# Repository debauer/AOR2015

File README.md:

AOR2015 - Fahrzeug Sensorik und Musik
=======

Project splittet

https://github.com/debauer/uboot-hardware  
https://github.com/debauer/uboot-software  
https://github.com/debauer/uboot-laser-parts  
https://github.com/debauer/uboot-firmware

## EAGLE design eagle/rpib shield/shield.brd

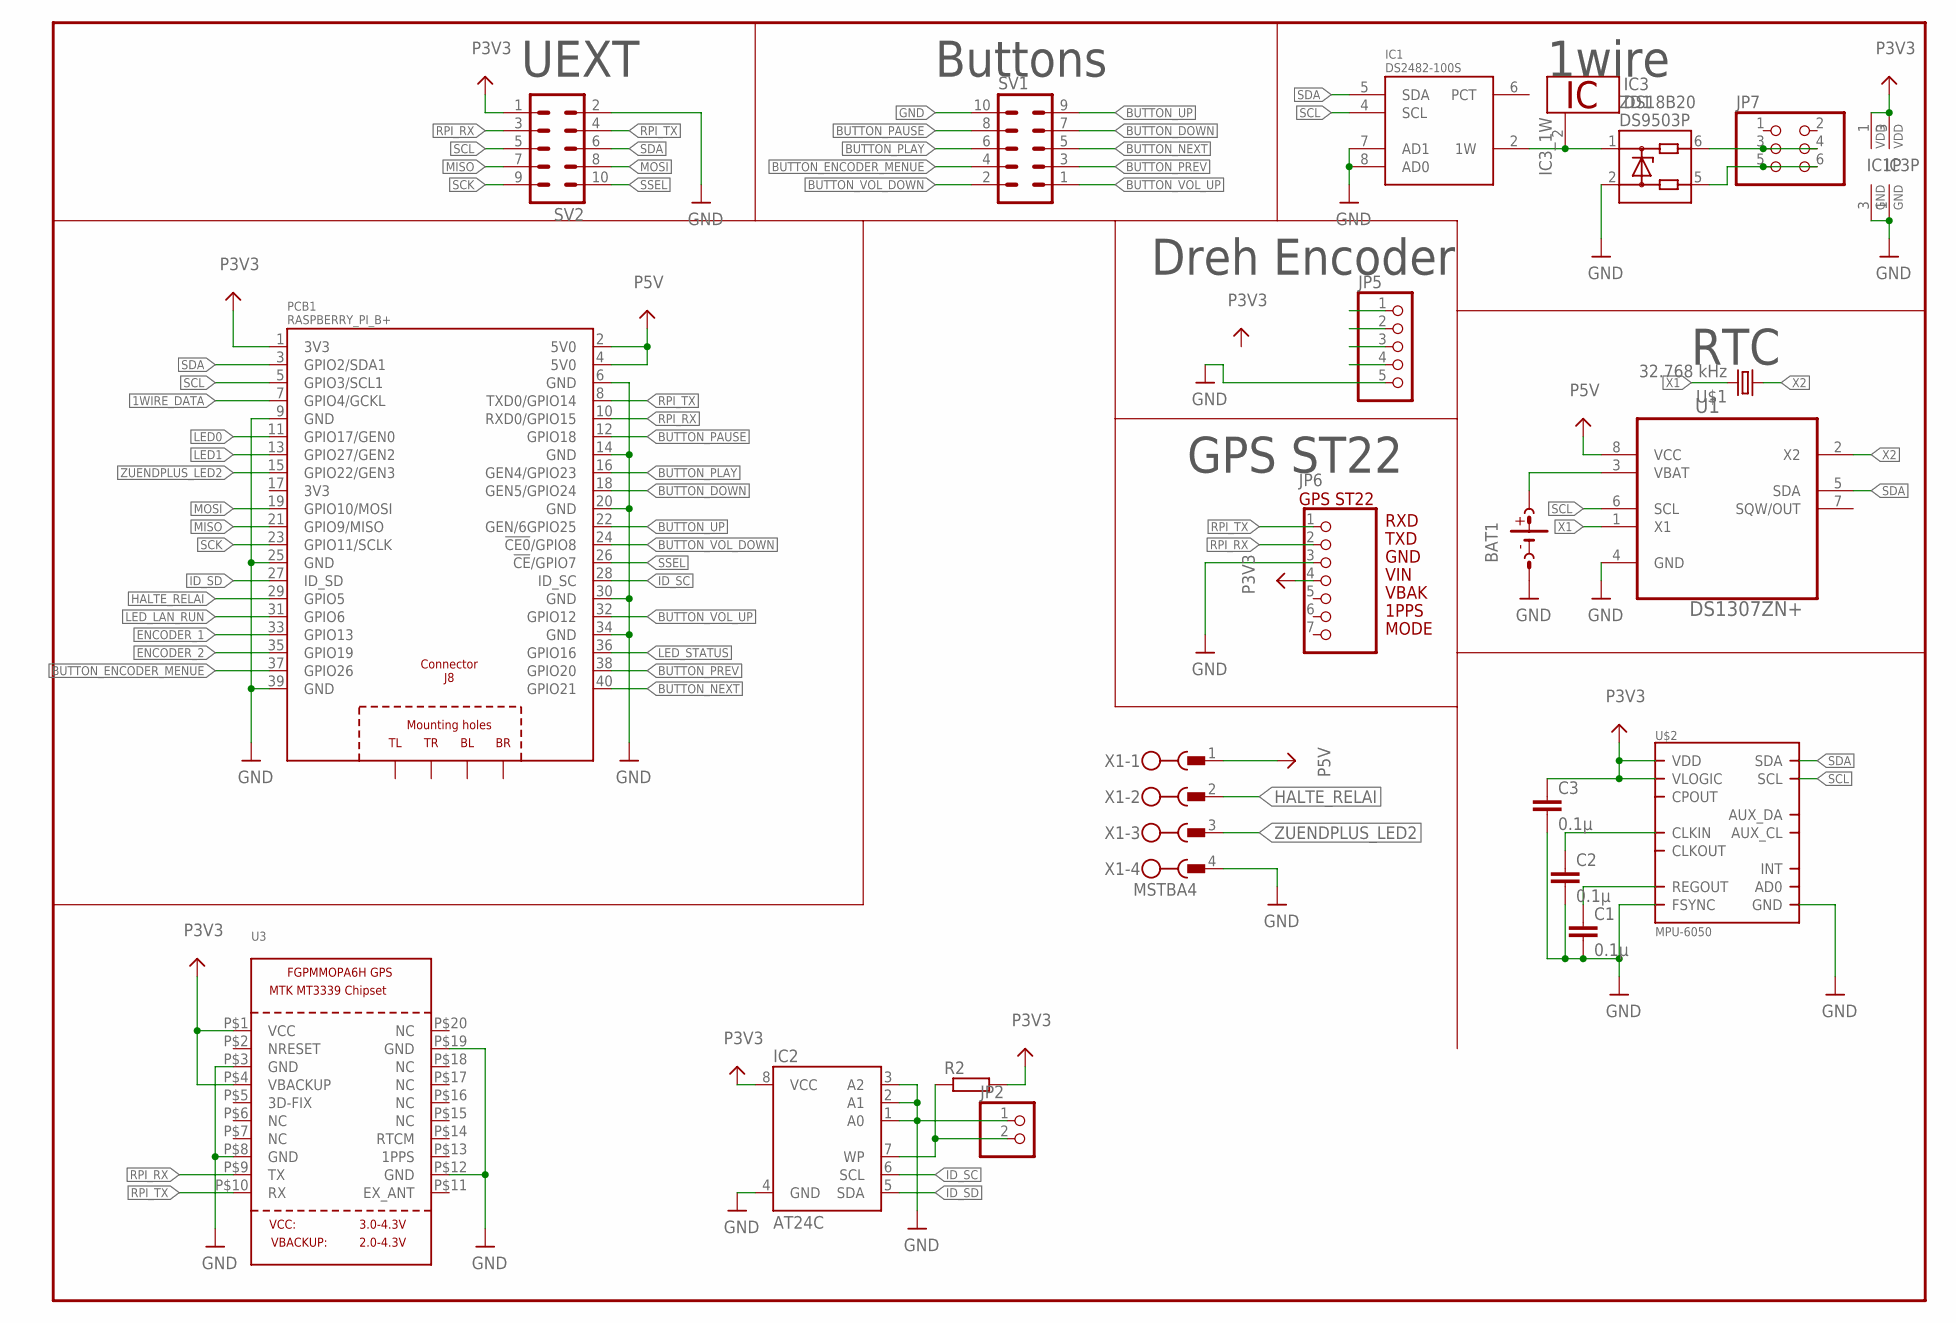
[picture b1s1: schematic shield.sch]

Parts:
BAT1: CR2032; CR2032-SOCKET
C1, C2, C3: 0.1µ; C0805
IC1: DS2482-100S; SO08
IC2: AT24C; SO08
IC3: DS18B20; TO92-
JP2: PINHD-1X2; 1X02
JP5: PINHD-1X5/90; 1X05/90
JP6: GPS_ST22; 1X07
JP7: PINHD-2X3/90; 2X03/90
PCB1: RASPBERRY_PI_B+
R2: R-EU_R0805; R0805
SV1, SV2: ML10
U1: DS1307ZN+; SOIC127P600X175-8N
U3: GPS_FGPMMOPA6H; FGPMMOPA6H
U$1: 32.768 kHz; CC5
U$2: MPU-6050; QFN.24.4X4
X1: MSTBA4
ZD1: DS9503P; TSOC6

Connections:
1WIRE_DATA: IC1.2 (1W), IC3.2 (1W), PCB1.7 (GPIO4/GCKL), ZD1.1
BUTTON_DOWN: PCB1.18 (GEN5/GPIO24), SV1.7
BUTTON_ENCODER_MENUE: PCB1.37 (GPIO26), SV1.4
BUTTON_NEXT: PCB1.40 (GPIO21), SV1.5
BUTTON_PAUSE: PCB1.12 (GPIO18), SV1.8
BUTTON_PLAY: PCB1.16 (GEN4/GPIO23), SV1.6
BUTTON_PREV: PCB1.38 (GPIO20), SV1.3
BUTTON_UP: PCB1.22 (GEN/6GPIO25), SV1.9
BUTTON_VOL_DOWN: PCB1.24 (!CE0!/GPIO8), SV1.2
BUTTON_VOL_UP: PCB1.32 (GPIO12), SV1.1
ENCODER_1: PCB1.33 (GPIO13)
ENCODER_2: PCB1.35 (GPIO19)
GND: BAT1.M (NEG), C1.2, C2.2, C3.2, IC1.3 (GND), IC1.7 (AD1), IC1.8 (AD0), IC2.1 (A0), IC2.2 (A1), IC2.3 (A2), IC2.4 (GND), IC3.1 (GND), JP2.1, JP5.5, JP6.3, PCB1.6 (GND), PCB1.14 (GND), PCB1.20 (GND), PCB1.30 (GND), PCB1.34 (GND), SV1.10, SV2.2, U1.4 (GND), U3.P$3 (GND), U3.P$8 (GND), U3.P$12 (GND), U3.P$19 (GND), U$2.11 (FSYNC), U$2.18 (GND), X1.4, ZD1.2
GND@1: PCB1.9 (GND), PCB1.25 (GND), PCB1.39 (GND)
HALTE_RELAI: PCB1.29 (GPIO5), X1.2
ID_SC: IC2.6 (SCL), PCB1.28 (ID_SC)
ID_SD: IC2.5 (SDA), PCB1.27 (ID_SD)
LED0: PCB1.11 (GPIO17/GEN0)
LED1: PCB1.13 (GPIO27/GEN2)
LED_LAN_RUN: PCB1.31 (GPIO6)
LED_STATUS: PCB1.36 (GPIO16)
MISO: PCB1.21 (GPIO9/MISO), SV2.7
MOSI: PCB1.19 (GPIO10/MOSI), SV2.8
unnamed: BAT1.P (POS2), U1.3 (VBAT)
unnamed: C1.1, U$2.10 (REGOUT)
unnamed: C2.1, U$2.1 (CLKIN)
unnamed: IC2.7 (WP), JP2.2, R2.1
unnamed: JP7.3, JP7.4, ZD1.6
unnamed: JP7.5, JP7.6, ZD1.5
P3V3: C3.1, IC1.1 (VDD), IC2.8 (VCC), IC3.3 (VDD), JP6.4, PCB1.1 (3V3), R2.2, SV2.1, U3.P$1 (VCC), U3.P$4 (VBACKUP), U$2.8 (VLOGIC), U$2.13 (VDD)
P5V: PCB1.2 (5V0), PCB1.4 (5V0), U1.8 (VCC), X1.1
RPI_RX: JP6.2, PCB1.10 (RXD0/GPIO15), SV2.3, U3.P$9 (TX)
RPI_TX: JP6.1, PCB1.8 (TXD0/GPIO14), SV2.4, U3.P$10 (RX)
SCK: PCB1.23 (GPIO11/SCLK), SV2.9
SCL: IC1.4 (SCL), PCB1.5 (GPIO3/SCL1), SV2.5, U1.6 (SCL), U$2.23 (SCL)
SDA: IC1.5 (SDA), PCB1.3 (GPIO2/SDA1), SV2.6, U1.5 (SDA), U$2.24 (SDA)
SSEL: PCB1.26 (!CE!/GPIO7), SV2.10
X1: U1.1 (X1), U$1.P$2 (2)
X2: U1.2 (X2), U$1.P$1 (1)
ZUENDPLUS_LED2: PCB1.15 (GPIO22/GEN3), X1.3

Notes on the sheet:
1wire
Dreh Encoder
RTC
UEXT
GPS ST22
Buttons

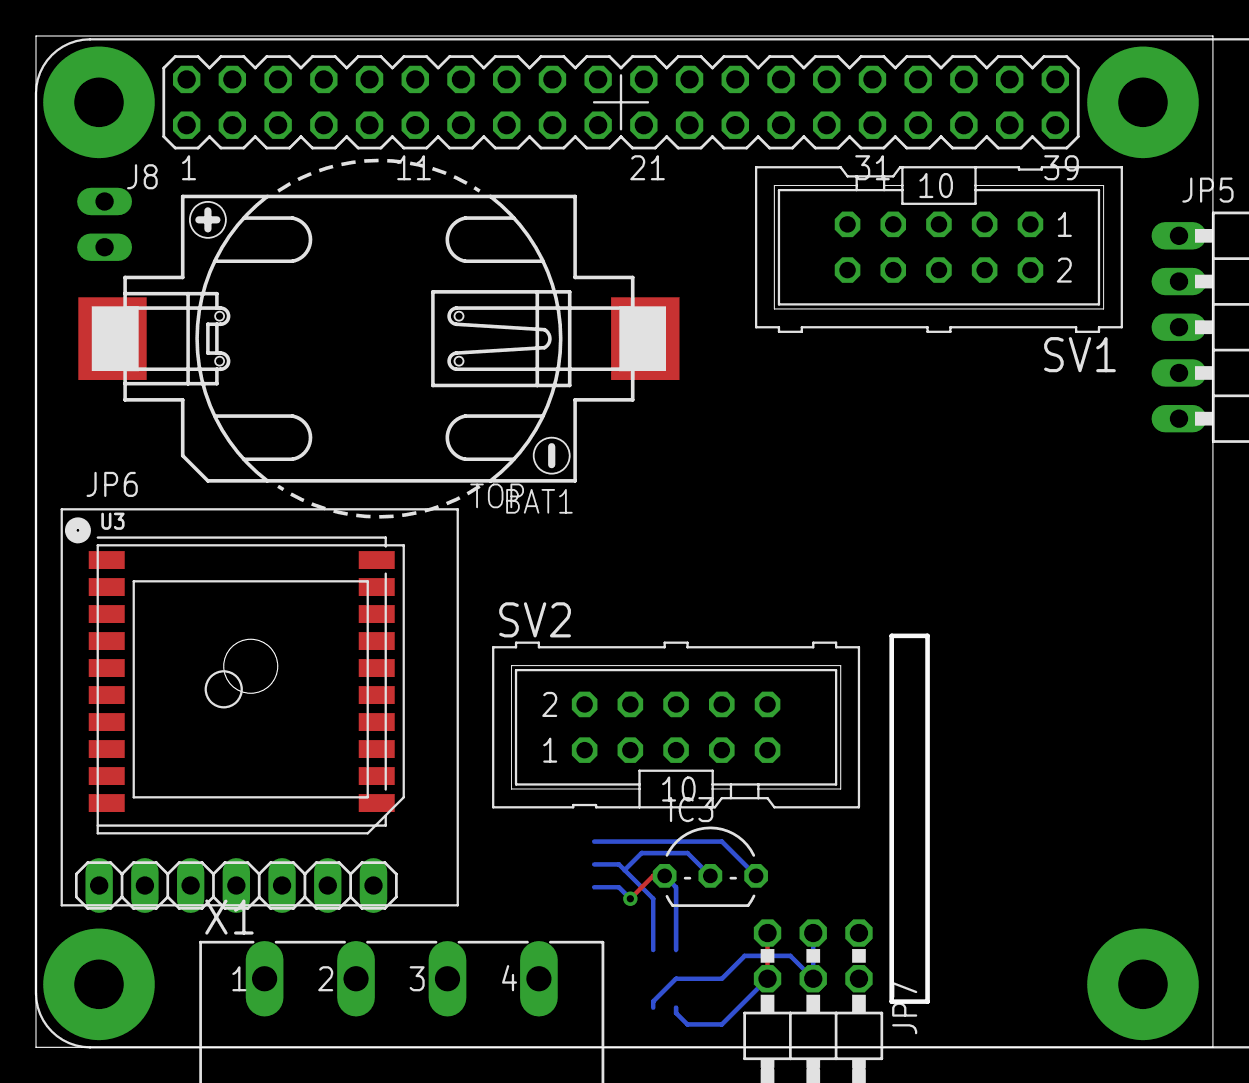
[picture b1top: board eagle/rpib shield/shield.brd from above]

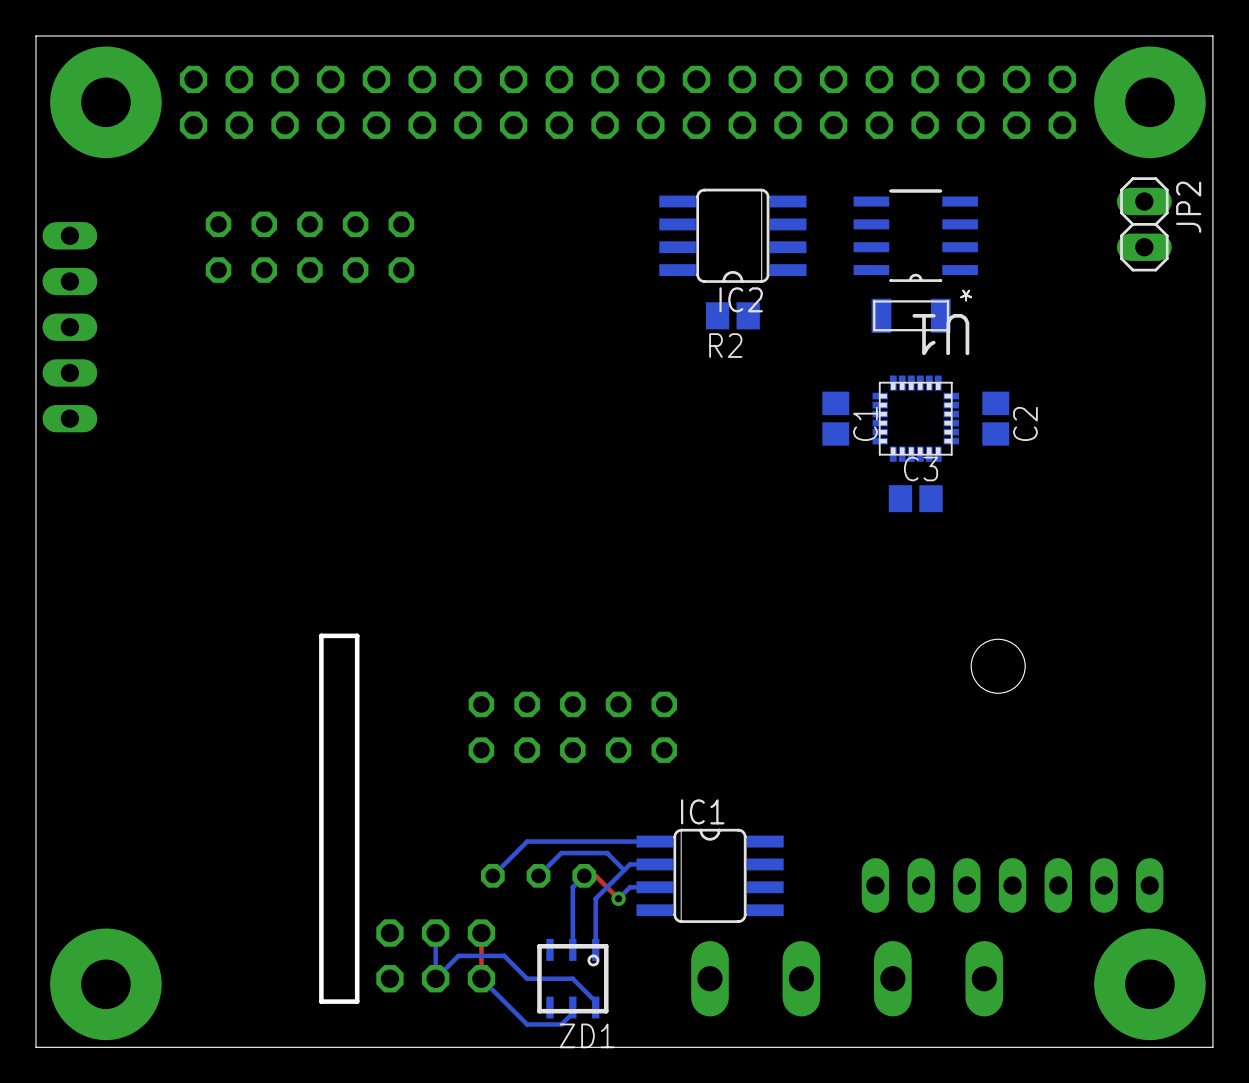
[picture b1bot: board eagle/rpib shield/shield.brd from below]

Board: 2 copper layers, 65.4 x 56.2 mm, 21 parts (11 on the bottom side), 34 nets.

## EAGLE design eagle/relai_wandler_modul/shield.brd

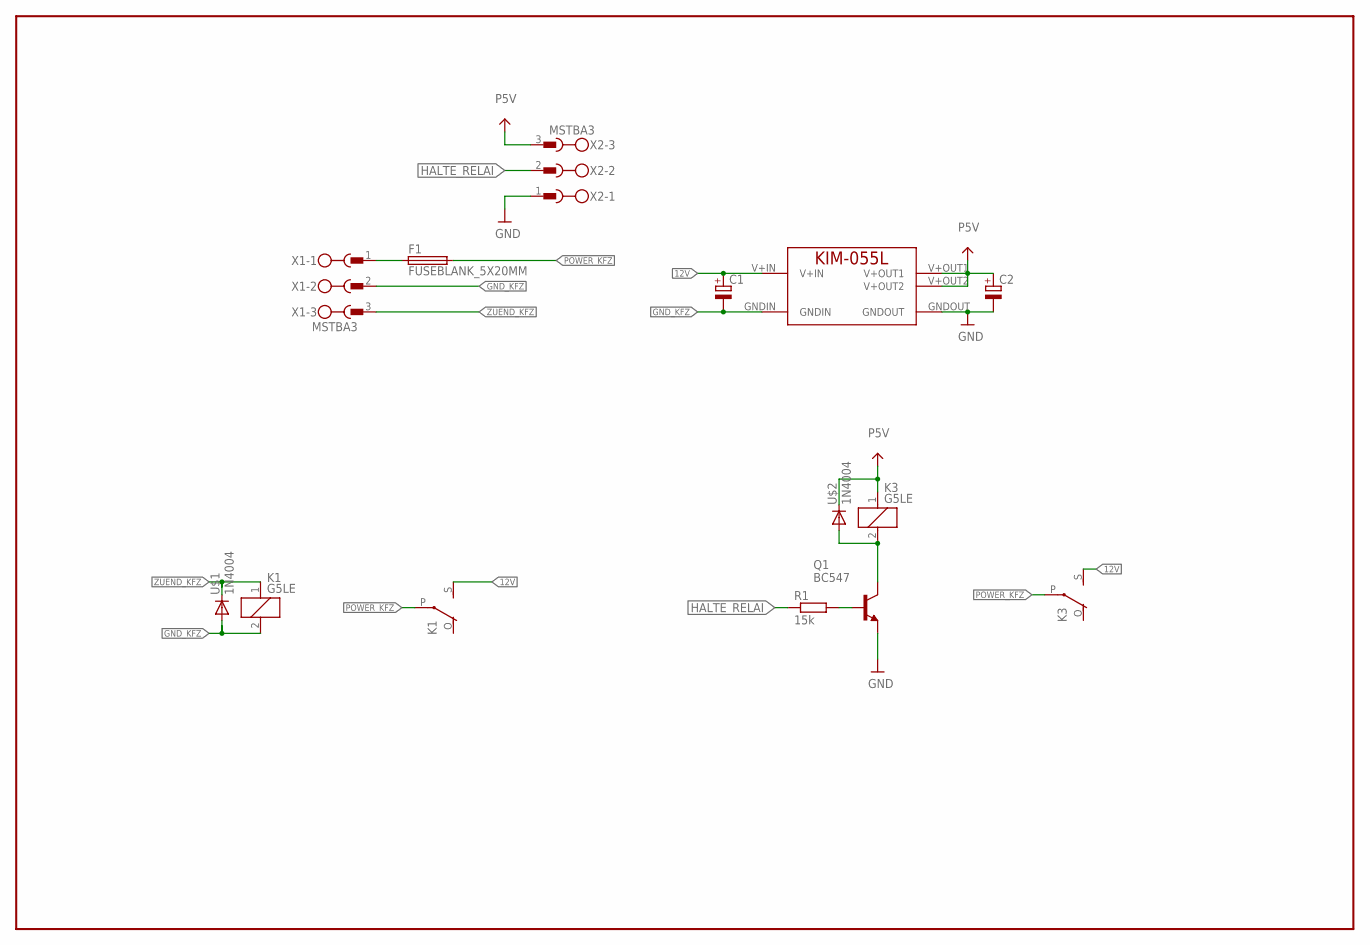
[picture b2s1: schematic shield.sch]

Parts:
C1, C2: CPOL-EUE5-13; E5-13
F1: FUSEBLANK_5X20MM; FUSE_HOLDER_5X20MM
K1, K3: G5LE
MOD1: KIM-055L
Q1: BC547; TO92
R1: 15k; 0207/7
U$1, U$2: 1N4004; DO41-10
X1, X2: MSTBA3

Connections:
12V: C1.+, K1.S, K3.S, MOD1.V+IN
GND: C2.-, MOD1.GNDOUT, Q1.1 (E), X2.1
GND_KFZ: C1.-, K1.2, MOD1.GNDIN, U$1.A, X1.2
HALTE_RELAI: R1.1, X2.2
unnamed: K3.2, Q1.3 (C), U$2.A
unnamed: Q1.2 (B), R1.2
unnamed: F1.1, X1.1
P5V: C2.+, K3.1, MOD1.V+OUT1, MOD1.V+OUT2, U$2.C, X2.3
POWER_KFZ: F1.2, K1.P, K3.P
ZUEND_KFZ: K1.1, U$1.C, X1.3

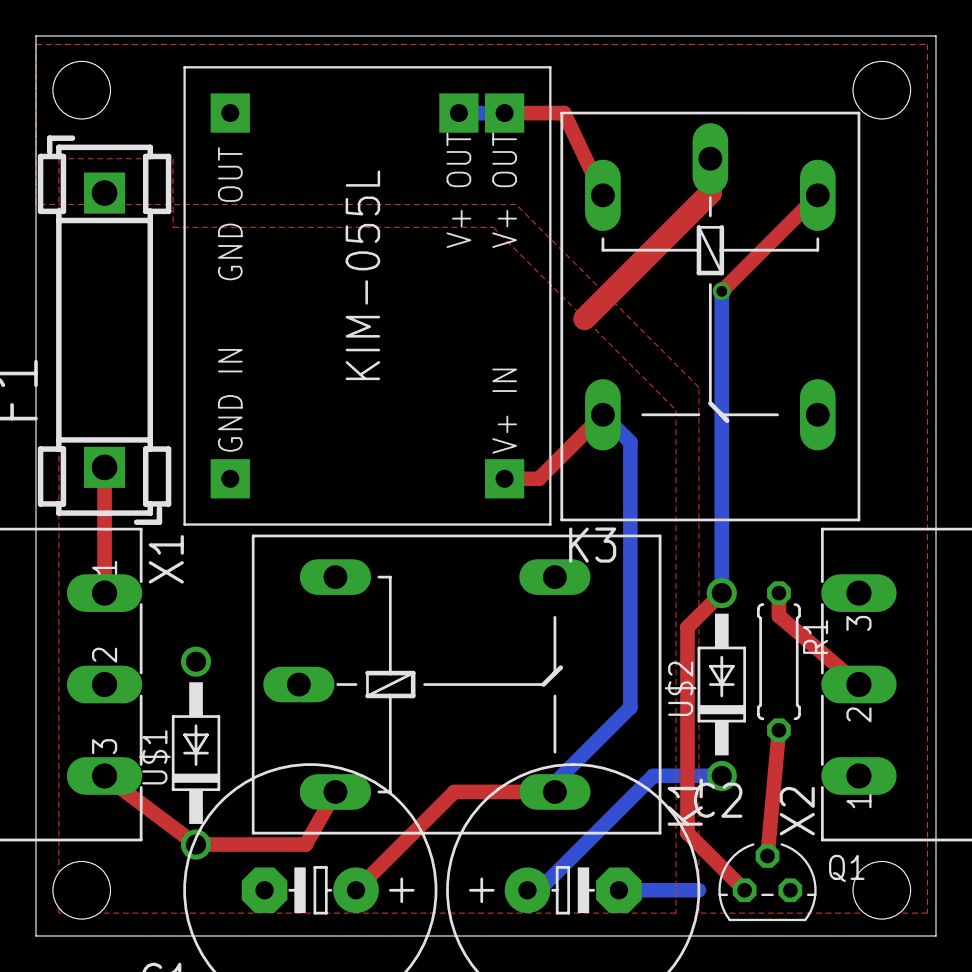
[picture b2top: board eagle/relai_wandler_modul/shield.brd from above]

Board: 2 copper layers, 50.0 x 50.0 mm, 12 parts (0 on the bottom side), 10 nets.

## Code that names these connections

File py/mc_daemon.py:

#!/usr/bin/python
#
#music and control daemon

from subprocess import *
import os,sys,time,serial,json,psutil
import pymongo
from pymongo import MongoClient
from bson import BSON
from bson import json_util
import RPi.GPIO as GPIO

config = json.loads(open('../configs/aor_service.json').read())

logging_info = config['logging']['logger']['info']
logging_error = config['logging']['logger']['error']
store_mongo = config['store']['mongo']
store_influx = config['store']['influx']
store_redis = config['store']['redis']
store_rrd = config['store']['rrd']
playlist_lines = config['music']['playlist_lines']
hostname = config['hostname']
circle_sleep = int(config['circle_sleep'])
telegram_sleep = float(config['telegram_sleep'])

use_serial = True

lcd_seite = 0

GPIO.setmode(GPIO.BOARD)
#GPIO.setwarnings(False) 

ENCODER_1 		= 33
ENCODER_2 		= 35
BUTTON_ENCODER  = 37
BUTTON_NEXT		= 40
BUTTON_PREV		= 38
BUTTON_UP		= 22
BUTTON_DOWN		= 18

GPIO.setup(ENCODER_1, 		GPIO.IN, pull_up_down = GPIO.PUD_UP)
GPIO.setup(ENCODER_2, 		GPIO.IN, pull_up_down = GPIO.PUD_UP)
GPIO.setup(BUTTON_ENCODER, 	GPIO.IN, pull_up_down = GPIO.PUD_UP)
GPIO.setup(BUTTON_NEXT, 	GPIO.IN, pull_up_down = GPIO.PUD_UP) 
GPIO.setup(BUTTON_PREV,		GPIO.IN, pull_up_down = GPIO.PUD_UP) 
GPIO.setup(BUTTON_UP, 		GPIO.IN, pull_up_down = GPIO.PUD_UP) 
GPIO.setup(BUTTON_DOWN, 	GPIO.IN, pull_up_down = GPIO.PUD_UP) 

mpc = {}

if(store_mongo):
	import pymongo
	mongo = pymongo.MongoClient()
	#mongo = MongoClient('mongodb://localhost:27017/')
	mongo_db = mongo.rallye
	mongo_values = mongo_db.values



def run_cmd(cmd):
	p = Popen(cmd, shell=True, stdout=PIPE)
	output = p.communicate()[0]
	return output

if(use_serial):
	ser = serial.Serial('/dev/ttyACM0', 9600, timeout=1)
	time.sleep(3)

def mpc_cmd(cmd):
	return run_cmd('mpc ' + cmd)

def update_mpd_to_db():
	run_cmd('mpc current')[:22]

def serial_write(str):
	time.sleep(telegram_sleep)
	if(use_serial):
		print "ON: " +  str
		ser.write(str)
	else:
		print "OFF: " +  str

def mpc_get_stats():
	s =  mpc_cmd('stats')
	l = s.split('\n')
	return {"artists": int(l[0][8:]),
			"albums": int(l[1][7:]),
			"songs": int(l[2][6:]),
			"play_time": l[4][10:],
			"uptime": l[5][7:],
			"db_updated": l[6][11:],
			"db_play_time": l[7][13:]
		}

def mpc_get_song():
	return run_cmd('mpc current')

def mpc_get_status1():
	s =  mpc_cmd('')
	if(s[0:6] != "volume"):
		a = s.split('\n')
		d = a[1]
	else:
		d = ""
	status = {}
	if(d!=""):
		status["position"] = d[11:16] 
		status["time"] = d[19:28]
		if(d[:9] == "[paused]"):
			status["title"] = d[10:]
		elif(d[:9] == "[playing]"):
			status["title"] = d[11:]
	#print status["title"]
	return status

def mpc_get_status2():
	s =  mpc_cmd('')
	if(s[0:6] != "volume"):
		a = s.split('\n')
		l = a[2]
	else:
		l = s
	status = {"volume": l[7:10],"repeat": l[22:25],"random": l[36:39],"single": l[50:53],"consume": l[65:68],"position": "xx/xx","title": ""}
 	return status

def cleanup():
	if(use_serial):
		ser.close()
	GPIO.cleanup()

def mpc_get_playlist(inc,length = 4):
	p =  mpc_cmd('playlist')
	playlist = p.split('\n')
	partlist = []
	if(inc>=len(playlist)):
		inc = 0
	if(len(playlist)> inc+length):
		for i in range(inc,inc+length):
			partlist.append(playlist[i])
	else:
		for i in range(inc,len(playlist)):
			partlist.append(playlist[i])
		#print inc+length-len(playlist)
		for i in range(inc+length-len(playlist)+1):
			partlist.append(playlist[i])
	return partlist

def mongo_select(key):
	if(store_mongo):
		s = mongo_values.find_one({"key":key})
		if s:
			return s["value"]
		else:
			return ""

def serial_send_mpd(id):
	global mpc
	song = mpc_get_song()[:24]
	song_status = mpc_get_status1()
	status = mpc_get_status2()
	if(song != mpc["song"] or id == -2):
		mpc["song"] = song
		if(id == 0 or id < 0):
			serial_write("mpd 0 "+ mpc["song"] + " \r")
	if(song_status != mpc["song_status"] or id == -2):
		mpc["song_status"] = song_status
		if(id == 1 or id < 0):
			serial_write("mpd 1 "+ mpc["song_status"]["title"] + " \r")
	if(status != mpc["status"] or id == -2):
		if(id == 2 or id < 0):
			mpc["status"] = status
			serial_write("mpd 2 V: " + mpc["status"]["volume"] + "%  RE: " + mpc["status"]["repeat"] +"  RE: " + mpc["status"]["random"] +"\r")

def serial_send_values():
	if(store_mongo):
		temperatur = mongo_select("cpu_temperatur")
		temperatur_format = "{:4.1f}".format(temperatur)
		serial_write("value 2 "+ temperatur_format + " \r")

def mpc_next(channel):
	mpc_cmd("next")
	print("Button next pressed")

def mpc_prev(channel):
	mpc_cmd("prev")
	print("Button prev pressed")

GPIO.add_event_detect(BUTTON_NEXT, GPIO.FALLING, callback=mpc_next, bouncetime=300)
GPIO.add_event_detect(BUTTON_PREV, GPIO.FALLING, callback=mpc_prev, bouncetime=300)

try:
	mpc["song_status"] = mpc_get_status1()
	mpc["status"] = mpc_get_status2()
	mpc["song"] = mpc_get_song()[:24]
	serial_send_mpd(-2)
	while 1:
		#print mpc_get_status2()
		#print mpc_get_song()
		#print mpc_get_stats()
		time.sleep(circle_sleep)
		if lcd_seite == 0:
			# |   artist 1 - song 123    |
			# |  #12/24 1:24/4:31 (34%)  |
			# | V: 51%  RE: off  RA: off |
			serial_send_values()
			serial_send_mpd(-1)

except KeyboardInterrupt:
	print "KeyboardInterrupt"

except:
	print sys.exc_info()
	print "other error"

finally:
    cleanup()

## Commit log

2014-12-26 SocketStream Init
2014-12-30 added frontblende
2015-02-15 remote scripts & DIN Display Firmware init
2015-02-15 son fucking fuck!
2015-02-16 die scheisse funzt!
2015-02-16 chacka
2015-02-16 genuch!
2015-02-17 very naaaais
2015-02-17 update lcd from rpi tuut
2015-02-18 MPD Daten werden angezeigt
2015-03-11 wireless_unit
2015-03-23 somesing
2015-03-23 morbi <3
2015-03-24 much many grafana improvements
2015-03-24 readme update
2015-03-24 added INSTALL_RPI2.md
2015-03-25 scripts improvements and new manuals
2015-03-25 improvements in logger script
2015-03-25 mpc ansteuerung begonnen
2015-03-25 dont know what i'm doing
2015-03-26 dumdidum
2015-03-26 oehm
2015-03-26 cleanup
2015-03-30 backup.md update
2015-04-17 some work on daemons
2015-05-03 viel umgebaut. großer performance gewinn
2015-07-29 deleted all files because of repo split
